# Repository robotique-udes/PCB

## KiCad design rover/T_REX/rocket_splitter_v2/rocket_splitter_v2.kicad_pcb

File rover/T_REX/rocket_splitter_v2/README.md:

# PDB (Power Distribution Board)
PCB servant diviser le signal et le power aux deux moteurs pour chaque côté

Voici les informations concernant le PCB : PDB

## Image du PCB en 3D

## Objectifs:
* Envoyer le même signal de commande au moteur avant qu'en arrière (pour un Rocker).
* Alimenter deux PCB de Drive de moteur à l'aide d'une seule entrée de courant. 

## Composants principaux:
* XT60PW-F (Connecteur Power Moteur)
* XT60PW-M (Connecteur Vers une alimentation)
* AMPHENOL_54601 (Connecteur Ethernet Horizontaux)
* 3550 x2 (Socket de Fusibles)

## Fonctionnement:
Le circuit transfert le signal de commande du CAN bus vers deux prises qui vont vers les drivers de moteurs.
Le circuit l'alimentation en entrée vers les sorties pour alimenter les drivers de moteurs.

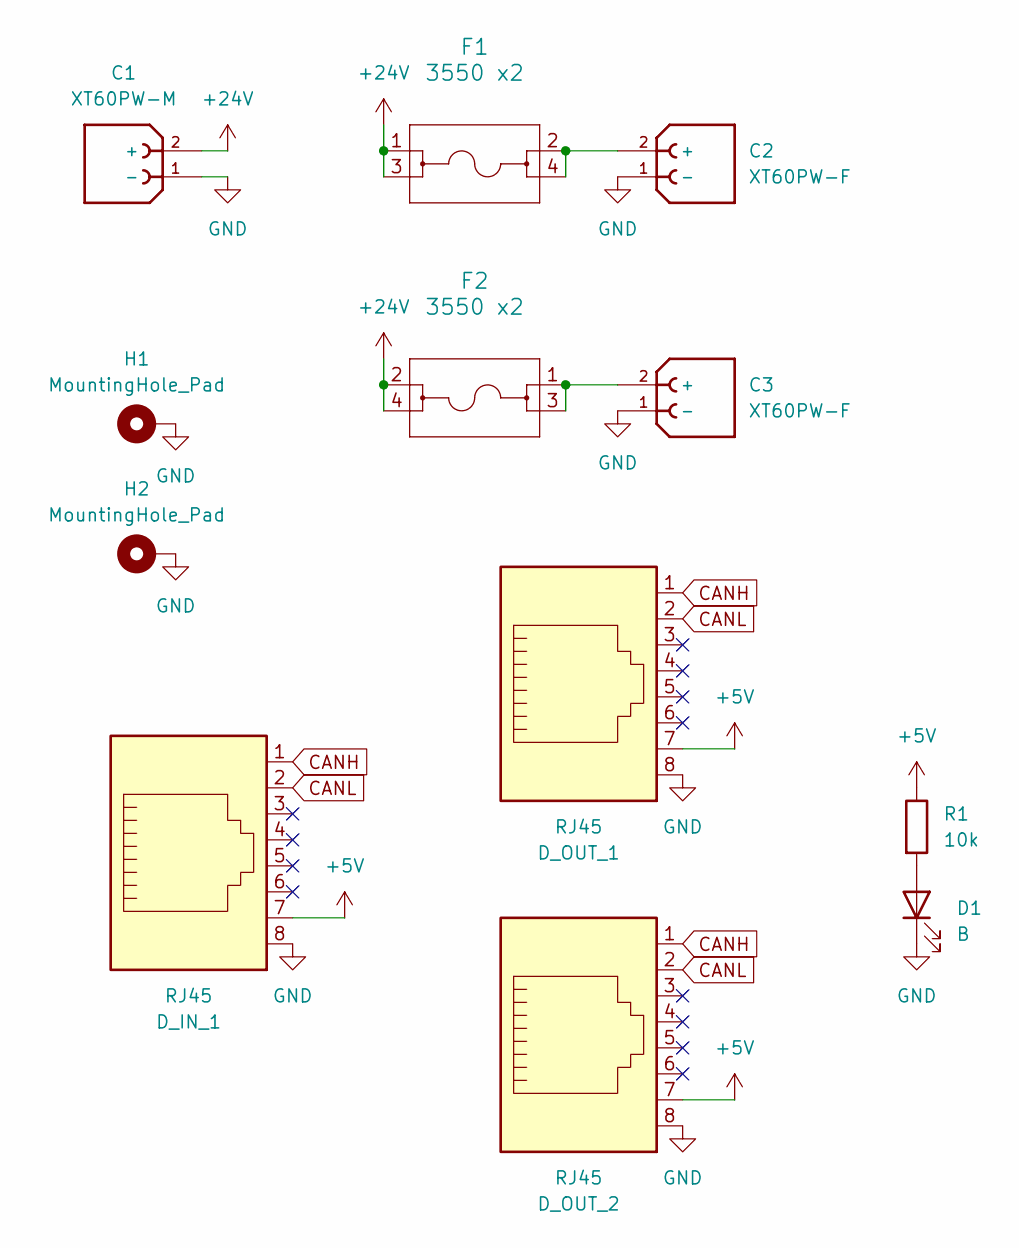
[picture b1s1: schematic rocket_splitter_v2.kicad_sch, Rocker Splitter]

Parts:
C1: XT60PW-M; AMASS_XT60PW-M_1x02_P7.20mm_Horizontal
C2, C3: XT60PW-F; AMASS_XT60PW-F_1x02_P7.20mm_Horizontal
D1: B; LED_0805_2012Metric_Pad1.15x1.40mm_HandSolder
D_IN_1: RJ45; AMPHENOL_54601-908WPLF
D_OUT_1, D_OUT_2: RJ45; AMPHENOL_54601-908WPLF
F1, F2: 3550 x2; 3550-2_KEY
H1, H2: MountingHole_Pad; MountingHole_5.3mm_M5_DIN965_Pad_TopBottom
R1: 10k; R_0805_2012Metric_Pad1.20x1.40mm_HandSolder

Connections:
+5V: D_IN_1.7, D_OUT_1.7, D_OUT_2.7, R1.1
+24V: C1.2 (+), F1.1, F1.3, F2.2, F2.4
CANH: D_IN_1.1, D_OUT_1.1, D_OUT_2.1
CANL: D_IN_1.2, D_OUT_1.2, D_OUT_2.2
GND: C1.1 (-), C2.1 (-), C3.1 (-), D1.1 (K), D_IN_1.8, D_OUT_1.8, D_OUT_2.8, H1.1, H2.1
unnamed: C2.2 (+), F1.2, F1.4
unnamed: C3.2 (+), F2.1, F2.3
unnamed: D1.2 (A), R1.2

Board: 4 copper layers, 12 parts (0 on the bottom side), 8 nets, no tracks yet.

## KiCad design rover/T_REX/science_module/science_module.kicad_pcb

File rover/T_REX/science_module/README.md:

# PCB du module science

## Image du PCB en 3D

## Objectifs:
* Contrôller les actionneurs du module science
  * Fan
  * Moteur DC (Grinder)
  * Actuateur linéaire
  * 4x servos
* PDB pour ces actionneurs
* Communication avec le reste du Rover

## Composants principaux:
* ESP32 S3 WROOM
* Connecteur Ethernet
* 2x bouton
* Connecteur XT60 mâle
* 6x connecteur XT30 femelle
* 2x connecteur XT30 mâle
* 8x connecteur à 2 pins
* Connecteur à 4 pins
* 6x slot à fusible
* LED

## Fonctionnement:
* Le PCB reçoit du 24V par le XT60
* Un buck down 24V -> 5V externe est connecté par deux XT30 (1 femelle, 1 mâle)
* Un buck down 24V -> 12V externe est connecté par deux XT30 (1 femelle, 1 mâle)
* Chacune des deux fans du vaccum a un connecteur XT30 à 12V
* Le grinder et l'actuateur linéaire sont chacun alimentés par un connecteurs XT30 à 24V
* LIN_IN_1 et LIN_IN_2 passent par un H-bridge et deviennet LIN+ et LIN- afin de pouvoir contrôller le sens de l'actuateur linéaire
* Les 8 connecteurs à 2 pins servent à ??????????? (Envoyer des signaux de contrôle? PB?)
* La pin 1 du ethernet est le CAN High et la pin 2 est le CAN Low

## PGIO:
### Outputs

| Name         | GPIO |Commentaires                |
|--------------|------|----------------------------|
| GRINDER_PWM  | IO10 |                            |
| PB_GRINDER   | IO11 |                            |PB -> outputs ou inputs? PB-> Push Button? Connecteurs?
| FAN_B_PWM    | IO3  |                            |
| FAN_A_PWM    | IO9  |                            |
| PB_VACCUM    | IO38 |                            |
| Servo_0      | IO7  |                            |
| Servo_1      | IO15 |                            |
| Servo_2      | IO16 |                            |
| Servo_3      | IO17 |                            |
| LIN_IN_1     | IO18 | Parle au H-Bridge          |Outputs pour l'actuateur linéaire?
| LIN_IN_2     | IO8  | Parle au H-Bridge          |
| PB_UP        | IO14 |                            |
| PB_DOWN      | IO21 |                            |
| PB_CAROUSSEL | IO12 |                            |
| PB_SPARE     | IO13 |                            |
| LED_BUILDIN  | IO5  |                            |À quoi sert cette LED?

### Inputs

| Name         | GPIO |Commentaires                |
|--------------|------|----------------------------|
| EN_PB        | EN   | Bouton Enable              |
| GPIO_0       | IO1  | Bouton Boot                |
| LS_EXT       | IO2  | Limit switch               |
| LS_RET       | IO3  | Limit switch               |

### Communication

| Name         | GPIO |Commentaires                |
|--------------|------|----------------------------|
| RXC          | IO47 | Parle au Ethernet (CanBus) |
| TXC          | IO48 | Parle au Ethernet (CanBus) |
| USB_N        | IO19 | Parle au port micro-SD     |
| USB_P        | IO20 | Parle au port micro-SD     |

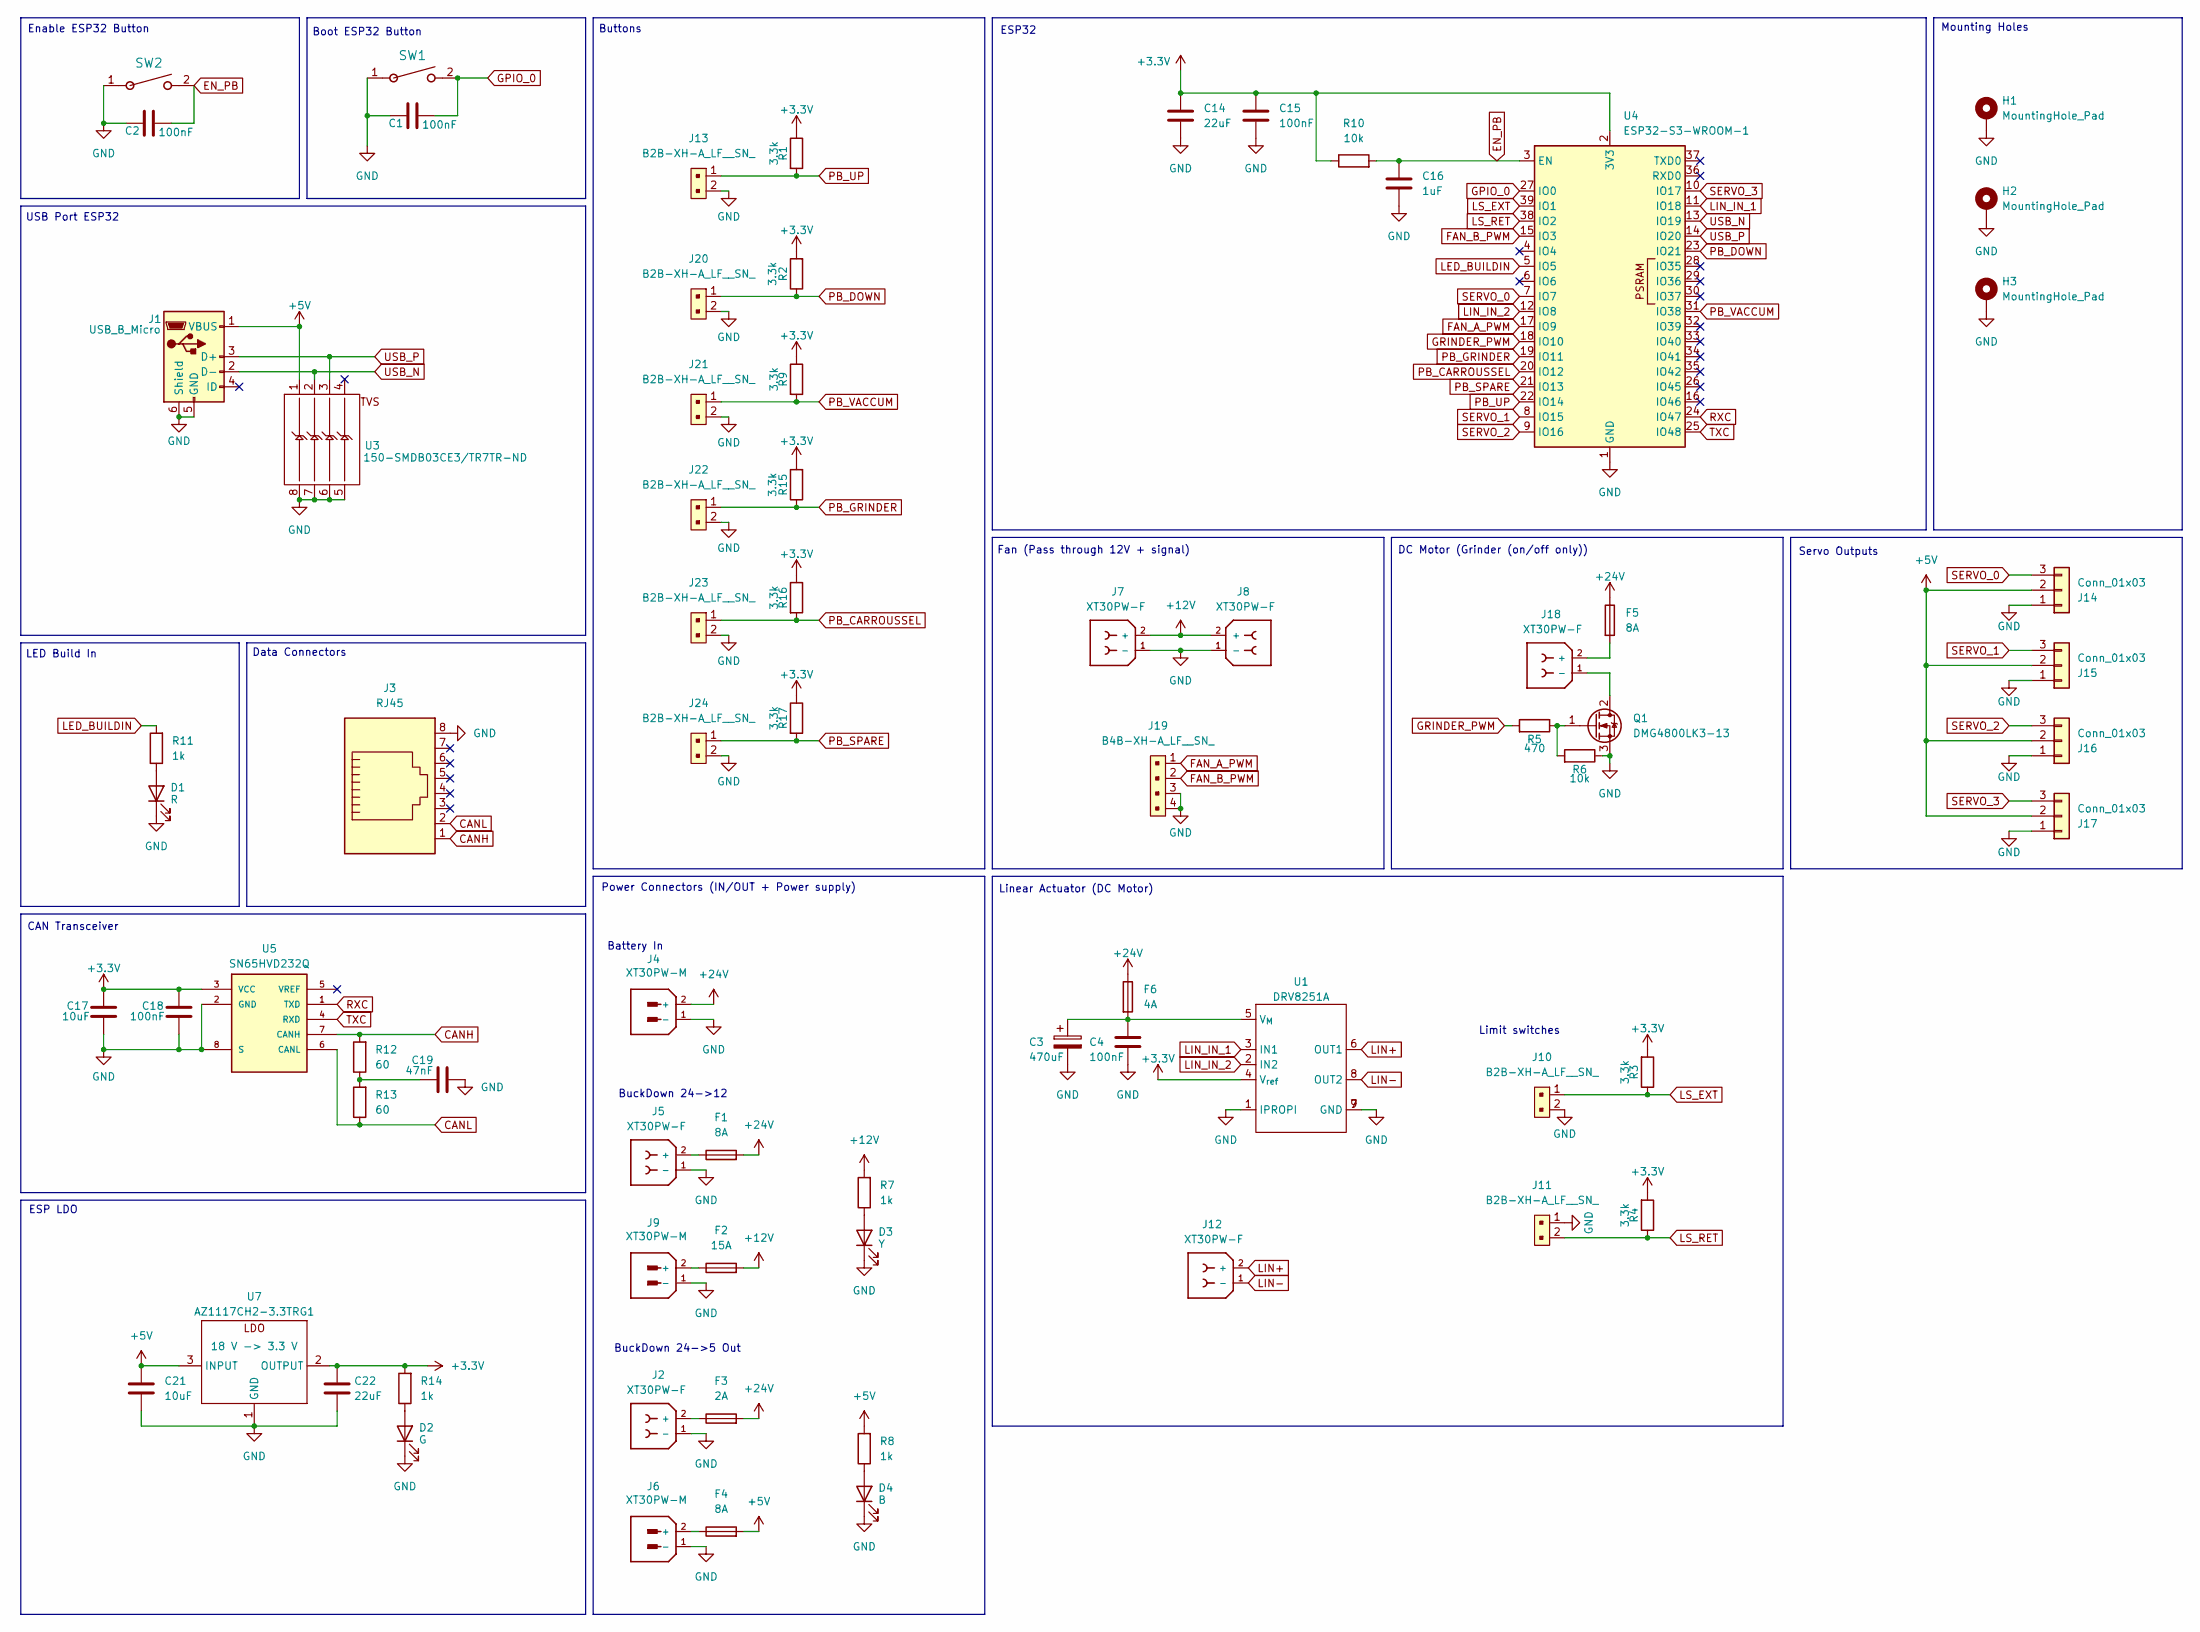
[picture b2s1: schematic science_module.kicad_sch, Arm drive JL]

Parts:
C1, C2, C4, C15, C18: 100nF; C_0805_2012Metric_Pad1.18x1.45mm_HandSolder
C3: 470uF; CP_Radial_D8.0mm_P3.50mm
C14, C22: 22uF; C_0805_2012Metric_Pad1.18x1.45mm_HandSolder
C16: 1uF; C_0805_2012Metric_Pad1.18x1.45mm_HandSolder
C17, C21: 10uF; C_0805_2012Metric_Pad1.18x1.45mm_HandSolder
C19: 47nF; C_0805_2012Metric_Pad1.18x1.45mm_HandSolder
D1: R; LED_0805_2012Metric_Pad1.15x1.40mm_HandSolder
D2: G; LED_0805_2012Metric_Pad1.15x1.40mm_HandSolder
D3: Y; LED_0805_2012Metric_Pad1.15x1.40mm_HandSolder
D4: B; LED_0805_2012Metric_Pad1.15x1.40mm_HandSolder
F1, F4, F5: 8A; FUSE_3568-20
F2: 15A; FUSE_3568-20
F3: 2A; FUSE_3568-20
F6: 4A; FUSE_3568-20
H1, H2, H3: MountingHole_Pad; MountingHole_3.2mm_M3_DIN965_Pad_TopBottom
J1: USB_B_Micro; USB_Micro-B_Amphenol_10118193-0001LF_Horizontal
J2, J5, J7, J8, J12, J18: XT30PW-F; AMASS_XT30PW-F_1x02_P2.50mm_Horizontal; PARTREV 1.2
J3: RJ45; ASSMANN_A-2014-2-4-N-T-R
J4: XT30PW-M; AMASS_XT60PW-M_1x02_P7.20mm_Horizontal; PARTREV 1.2
J6, J9: XT30PW-M; AMASS_XT30PW-M_1x02_P2.50mm_Horizontal; PARTREV 1.2
J10, J11, J13, J20, J21, J22, J23, J24: B2B-XH-A_LF__SN_; JST_XH_B2B-XH-A_1x02_P2.50mm_Vertical; MPN B2B-XH-A(LF)(SN); Digi-Key_PN 455-2247-ND
J14, J15, J16, J17: Conn_01x03; PinHeader_1x03_P2.54mm_Vertical
J19: B4B-XH-A_LF__SN_; JST_XH_B4B-XH-A_1x04_P2.50mm_Vertical; MPN B4B-XH-A(LF)(SN); Digi-Key_PN 455-2249-ND
Q1: DMG4800LK3-13; TO-252-2
R1, R2, R3, R4, R9, R15, R16, R17: 3.3k; R_0805_2012Metric_Pad1.20x1.40mm_HandSolder
R5: 470; R_0805_2012Metric_Pad1.20x1.40mm_HandSolder
R6, R10: 10k; R_0805_2012Metric_Pad1.20x1.40mm_HandSolder
R7, R8, R11, R14: 1k; R_0805_2012Metric_Pad1.20x1.40mm_HandSolder
R12, R13: 60; R_0805_2012Metric_Pad1.20x1.40mm_HandSolder
SW1, SW2: TS09-63-25-WT-160-SMT-TR; SW_TS09-63-25_CUD
U1: DRV8251A; Texas_HSOP-8-1EP_3.9x4.9mm_P1.27mm_ThermalVias
U3: 150-SMDB03CE3/TR7TR-ND; SOIC-8-1EP_3.9x4.9mm_P1.27mm_EP2.29x3mm
U4: ESP32-S3-WROOM-1
U5: SN65HVD232Q; SOIC127P600X175-8N; PARTREV 4
U7: AZ1117CH2-3.3TRG1; SOT-223-3_TabPin2

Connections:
+3.3V: C14.1, C15.1, C17.1, C18.1, C22.1, R1.1, R2.2, R3.2, R4.2, R9.1, R10.1, R14.2, R15.2, R16.1, R17.1, U1.4 (V_{ref}), U4.2 (3V3), U5.3 (VCC), U7.2 (OUTPUT)
+5V: C21.1, F4.2, J1.1 (VBUS), J14.2, J15.2, J16.2, J17.2, R8.2, U3.1, U7.3 (INPUT)
+12V: F2.2, J7.2 (+), J8.2 (+), R7.2
+24V: F1.2, F3.2, F5.1, F6.1, J4.2 (+)
CANH: J3.1, R12.2, U5.7 (CANH)
CANL: J3.2, R13.1, U5.6 (CANL)
EN_PB: C2.2, C16.1, R10.2, SW2.2, U4.3 (EN)
FAN_A_PWM: J19.1, U4.17 (IO9)
FAN_B_PWM: J19.2, U4.15 (IO3)
GND: C1.1, C2.1, C3.2, C4.2, C14.2, C15.2, C16.2, C17.2, C18.2, C19.1, C21.2, C22.2, D1.1 (K), D2.1 (K), D3.1 (K), D4.1 (K), H1.1, H2.1, H3.1, J1.5 (GND), J1.6 (Shield), J2.1 (-), J3.8, J4.1 (-), J5.1 (-), J6.1 (-), J7.1 (-), J8.1 (-), J9.1 (-), J10.2, J11.1, J13.2, J14.1, J15.1, J16.1, J17.1, J19.3, J19.4, J20.2, J21.2, J22.2, J23.2, J24.2, Q1.3 (S), R6.1, SW1.1, SW2.1, U1.1 (IPROPI), U1.7 (GND), U1.9 (GND), U3.5, U3.6, U3.7, U3.8, U4.1 (GND), U4.40 (GND), U4.41 (GND), U5.2 (GND), U5.8 (S), U7.1 (GND)
GPIO_0: C1.2, SW1.2, U4.27 (IO0)
GRINDER_PWM: R5.2, U4.18 (IO10)
LED_BUILDIN: R11.2, U4.5 (IO5)
LIN+: J12.2 (+), U1.6 (OUT1)
LIN-: J12.1 (-), U1.8 (OUT2)
LIN_IN_1: U1.3 (IN1), U4.11 (IO18)
LIN_IN_2: U1.2 (IN2), U4.12 (IO8)
LS_EXT: J10.1, R3.1, U4.39 (IO1)
LS_RET: J11.2, R4.1, U4.38 (IO2)
unnamed: C19.2, R12.1, R13.2
unnamed: D1.2 (A), R11.1
unnamed: D2.2 (A), R14.1
unnamed: D3.2 (A), R7.1
unnamed: D4.2 (A), R8.1
unnamed: F3.1, J2.2 (+)
unnamed: F1.1, J5.2 (+)
unnamed: F4.1, J6.2 (+)
unnamed: F2.1, J9.2 (+)
unnamed: F5.2, J18.2 (+)
unnamed: J18.1 (-), Q1.2 (D)
unnamed: Q1.1 (G), R5.1, R6.2
unnamed: C3.1, C4.1, F6.2, U1.5 (V_{M})
PB_CARROUSSEL: J23.1, R16.2, U4.20 (IO12)
PB_DOWN: J20.1, R2.1, U4.23 (IO21)
PB_GRINDER: J22.1, R15.1, U4.19 (IO11)
PB_SPARE: J24.1, R17.2, U4.21 (IO13)
PB_UP: J13.1, R1.2, U4.22 (IO14)
PB_VACCUM: J21.1, R9.2, U4.31 (IO38)
RXC: U4.24 (IO47), U5.1 (TXD)
SERVO_0: J14.3, U4.7 (IO7)
SERVO_1: J15.3, U4.8 (IO15)
SERVO_2: J16.3, U4.9 (IO16)
SERVO_3: J17.3, U4.10 (IO17)
TXC: U4.25 (IO48), U5.4 (RXD)
USB_N: J1.2 (D-), U3.2, U4.13 (IO19)
USB_P: J1.3 (D+), U3.3, U4.14 (IO20)

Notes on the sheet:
Boot ESP32 Button
LED Build In
Enable ESP32 Button
Servo Outputs
CAN Transceiver
Limit switches
DC Motor (Grinder (on/off only))
Power Connectors (IN/OUT + Power supply)
ESP LDO
Buttons
Data Connectors
BuckDown 24->12
BuckDown 24->5 Out
Mounting Holes
USB Port ESP32
Fan (Pass through 12V + signal)
Battery In
Linear Actuator (DC Motor)
ESP32

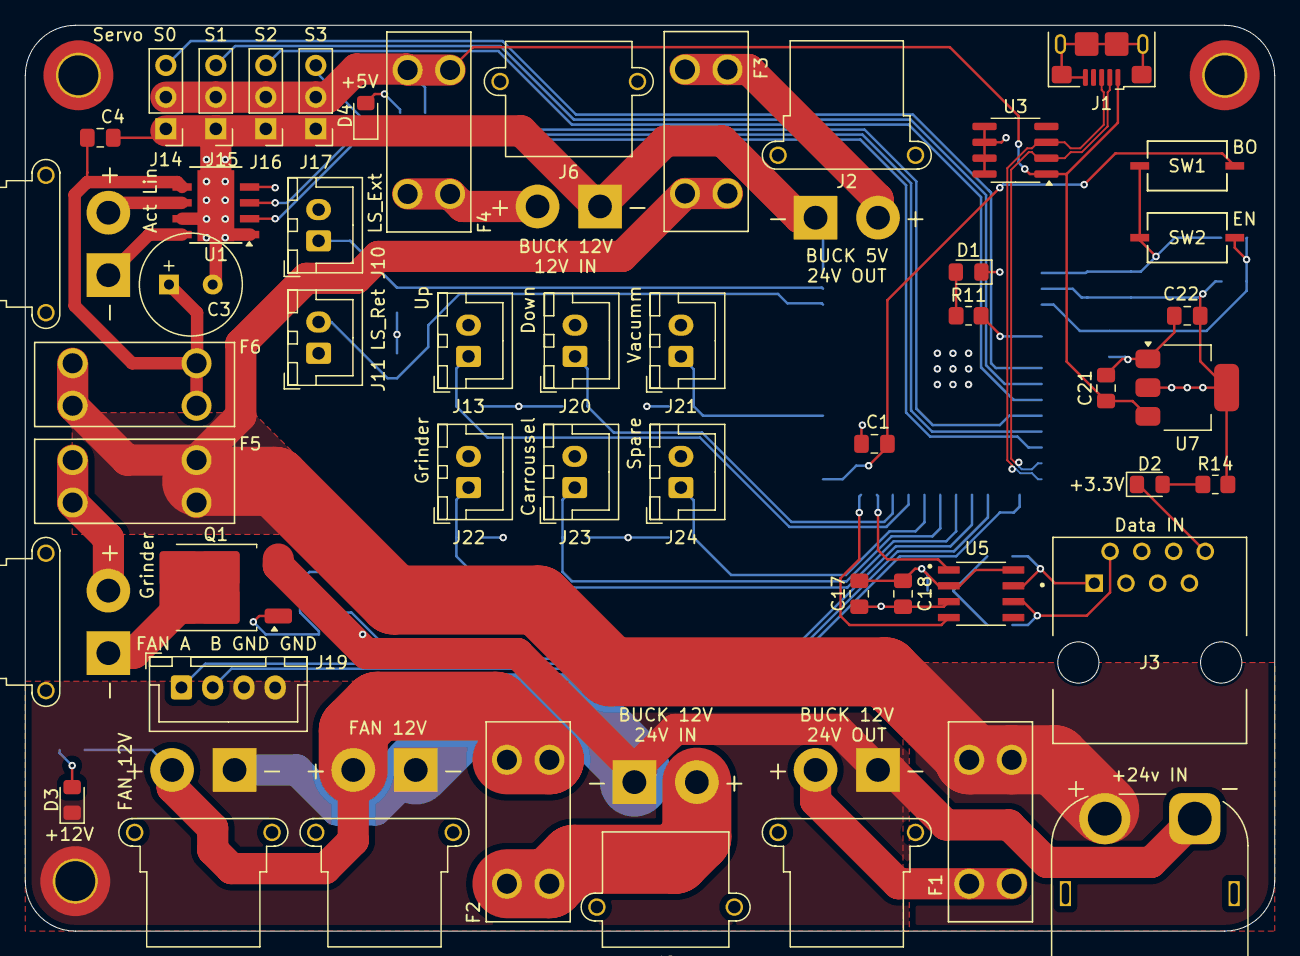
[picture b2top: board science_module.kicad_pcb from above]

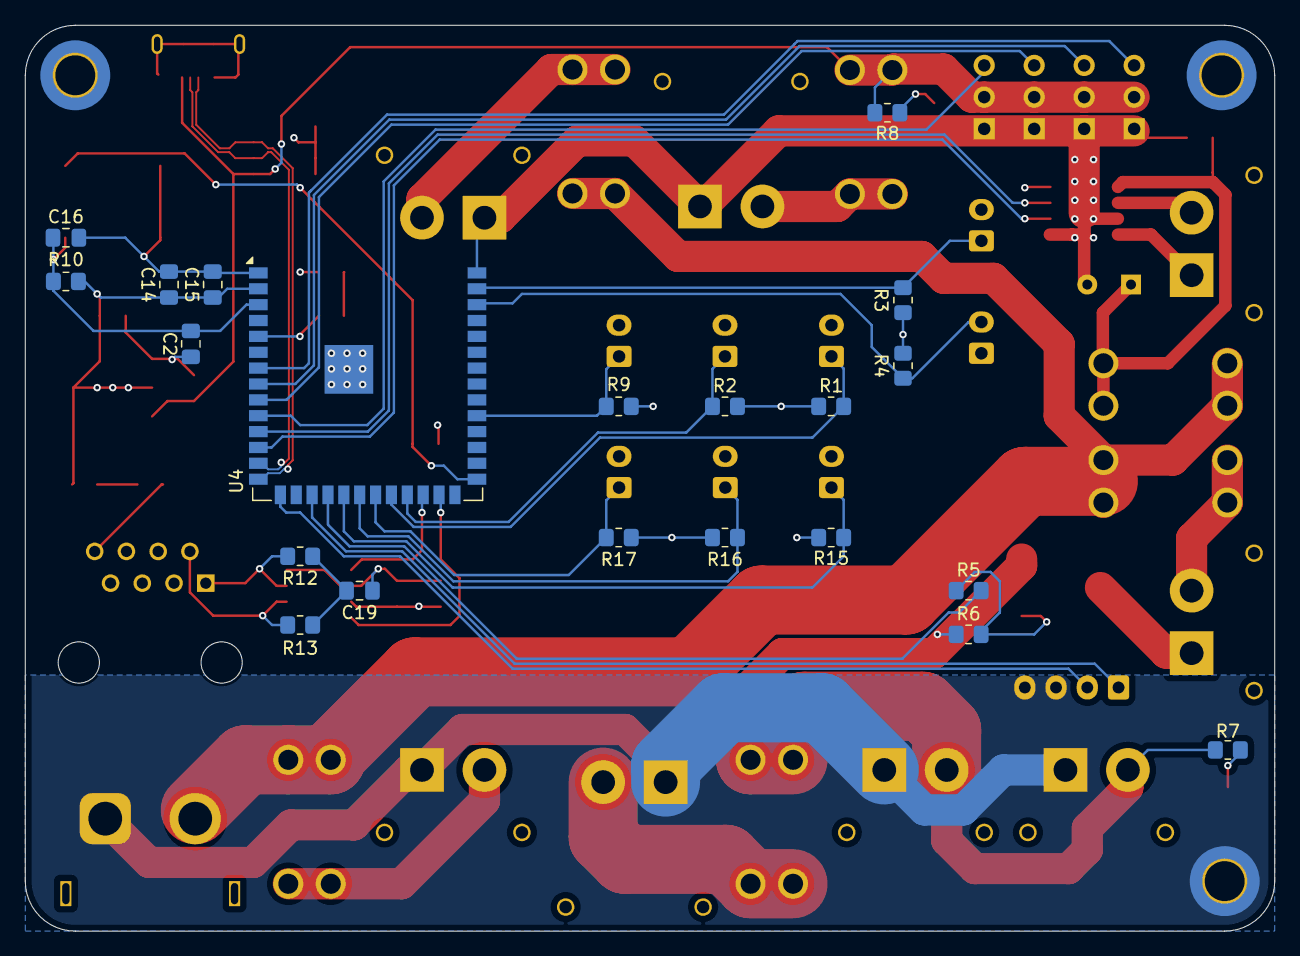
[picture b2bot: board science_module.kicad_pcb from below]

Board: 4 copper layers, 100.0 x 72.5 mm, 74 parts (21 on the bottom side), 46 nets.

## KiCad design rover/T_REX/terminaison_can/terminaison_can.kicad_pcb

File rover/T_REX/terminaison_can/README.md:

# Terminaison CAN bus
Petit PCB qui sert de terminaison aux extrémités du CAN bus.

## Image du PCB en 3D

## Objectifs:
* Requis de la couche transport du CanBus:
  * 2 terminaisons de 120 ohms doivent être branchés aux extrémités du bus.
    * Sur un bus OK on doit mesurer 60 Ohms
* Agir comme un indicateur visuel de s'il y a de l'alimentation en parallèle des lignes CanBus

## Composants principaux:
* Connecteur RJ45 pour câble ethernet
* 2x Résistances 60 ohms
* Condensateur 47nF
* Résistance 2k ohms
* DEL

## Fonctionnement:
Deux résistances de 60 ohms sont placées en série entre le CAN HIGH et le CAN LOW en une résistance combinée de 120 ohms, ce qui est le standard dans une terminaison CAN. La résistance permet de dissiper le signal passant dans le bus.

Le condensateur permet de créer un filtre passe-bas qui nettoie encore plus le signal.

Il y a aussi une résistance et une diode qui sont connectées entre le VCC et le GND afin d'indiquer visuellement (par une DEL allumée) qu'il y a du courant sur les pins 7 et 8.

## Références:
* https://electronics.stackexchange.com/questions/512653/can-split-termination-capacitor-calculation
* https://www.mouser.ca/datasheet/2/302/TJA1050-3083416.pdf

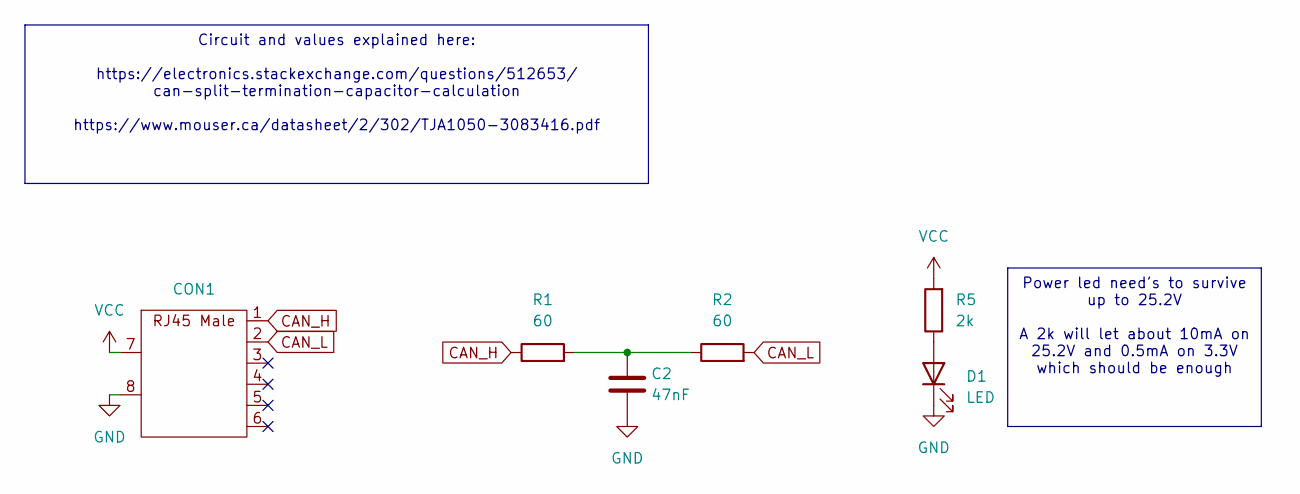
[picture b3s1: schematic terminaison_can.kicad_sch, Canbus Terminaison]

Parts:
C2: 47nF; C_0805_2012Metric_Pad1.18x1.45mm_HandSolder
CON1: RJ45_MALE-AJP92A8813
D1: LED; LED_0805_2012Metric_Pad1.15x1.40mm_HandSolder
R1, R2: 60; R_0805_2012Metric_Pad1.20x1.40mm_HandSolder
R5: 2k; R_0805_2012Metric_Pad1.20x1.40mm_HandSolder

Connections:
CAN_H: CON1.1, R1.1
CAN_L: CON1.2, R2.2
GND: C2.2, CON1.8, D1.1 (K)
unnamed: C2.1, R1.2, R2.1
unnamed: D1.2 (A), R5.1
VCC: CON1.7, R5.2

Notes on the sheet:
Power led need's to survive up to 25.2V A 2k will let about 10mA on 25.2V and 0.5mA on 3.3V which should be enough
Circuit and values explained here: https://electronics.stackexchange.com/questions/512653/ can-split-termination-capacitor-calculation https://www.mouser.ca/datasheet/2/302/TJA1050-3083416.pdf

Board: 2 copper layers, 6 parts (1 on the bottom side), 6 nets, no tracks yet.
